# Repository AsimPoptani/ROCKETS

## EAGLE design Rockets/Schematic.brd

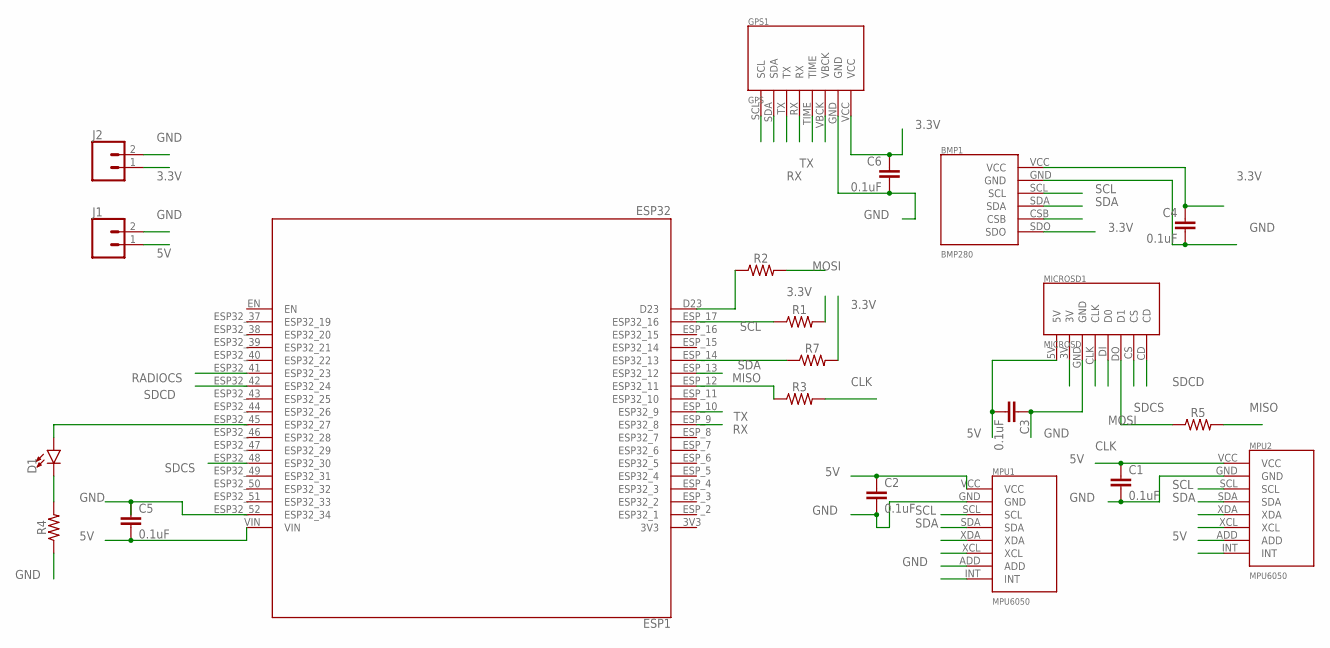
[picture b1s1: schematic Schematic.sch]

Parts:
BMP1: BMP280
C1, C2, C3, C4, C5, C6: 0.1uF; CAP-PTH-SMALL-KIT
D1: LED-3MM-NO_SILK; LED_3MM-NS
ESP1: ESP32
GPS1: GPS
J1, J2: CONN_02; 1X02
MICROSD1: MICROSD
MPU1, MPU2: MPU6050
R1, R2, R3, R4, R5, R7: AXIAL-0.3

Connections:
3.3V: BMP1.SDO, BMP1.VCC, C4.1, C6.1, GPS1.VCC, J2.1, R1.P$2 (2), R7.P$2 (2)
5V: C1.1, C2.1, C3.2, C5.2, ESP1.VIN, J1.1, MICROSD1.5V, MPU1.VCC, MPU2.ADD, MPU2.VCC
CLK: MICROSD1.CLK, R3.P$2 (2)
GND: BMP1.GND, C1.2, C2.2, C3.1, C4.2, C5.1, C6.2, ESP1.ESP32_52 (ESP32_34), GPS1.GND, J1.2, J2.2, MICROSD1.GND, MPU1.ADD, MPU1.GND, MPU2.GND, R4.P$1 (1)
MISO: ESP1.ESP_13 (ESP32_12), R5.P$2 (2)
MOSI: MICROSD1.DI (D0), R2.P$2 (2)
unnamed: ESP1.ESP_12 (ESP32_11), R3.P$1 (1)
unnamed: D1.A, ESP1.ESP32_45 (ESP32_27)
unnamed: D1.K (C), R4.P$2 (2)
unnamed: MICROSD1.DO (D1), R5.P$1 (1)
unnamed: ESP1.D23, R2.P$1 (1)
RADIOCS: ESP1.ESP32_41 (ESP32_23)
RX: ESP1.ESP_9 (ESP32_8), GPS1.TX
SCL: BMP1.SCL, ESP1.ESP_17 (ESP32_16), MPU1.SCL, MPU2.SCL, R1.P$1 (1)
SDA: BMP1.SDA, ESP1.ESP_14 (ESP32_13), MPU1.SDA, MPU2.SDA, R7.P$1 (1)
SDCD: ESP1.ESP32_42 (ESP32_24), MICROSD1.CD
SDCS: ESP1.ESP32_48 (ESP32_30), MICROSD1.CS
TX: ESP1.ESP_10 (ESP32_9), GPS1.RX

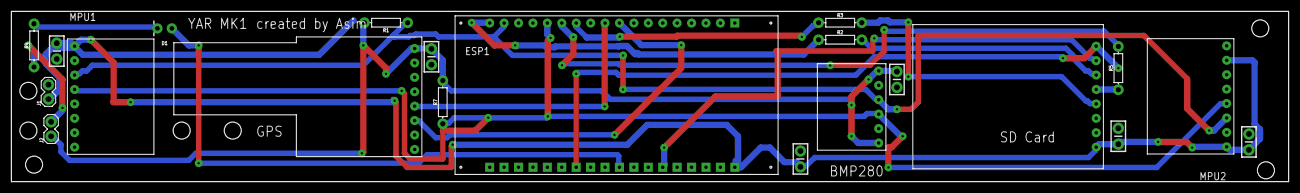
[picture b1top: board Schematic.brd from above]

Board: 2 copper layers, 225.0 x 30.0 mm, 21 parts (0 on the bottom side), 17 nets.

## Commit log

2021-08-18 Everthing added needs resistors
2021-08-23 Mk1 completed?
2021-08-23 updated libs
2021-08-31 Updated the schematics from discord zip

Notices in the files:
parts and their libraries:
SparkFun-Connectors: Licensing: Creative Commons ShareAlike 4.0 International - https://creativecommons.org/licenses/by-sa/4.0
